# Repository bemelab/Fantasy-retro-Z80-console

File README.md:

# Z80-retro-console

A browser-based Z80 fantasy console with its own programming language (**ZL**), a compiler that produces real Z80 machine code, and emulated display and sound chips. Everything is one self-contained file: `index.html`.

## Run it

Open `index.html` in any modern browser, or turn on GitHub Pages (Settings > Pages > Deploy from a branch > `main` / root) and open the page it gives you.

Press **Run** once so the browser allows sound.

## What is inside

- **CPU:** a full Z80 clocked at 4 MHz: every documented and undocumented instruction, all flags, interrupts (IM 0/1/2, NMI) and exact T-states, with 64 KB of memory. It passes the zexdoc and zexall instruction exercisers.
- **ZL language:** variables, `if`/`else`, `while`, `for`, arrays (1D and 2D), `gosub`/`goto`, `data` tables, sprites, text, and chip commands. It compiles to Z80 machine code.
- **Assembly listing:** every ZL line is shown with the Z80 instructions it produced, with comments.
- **Displays** (choose in the dropdown):
  - Virtual 64x64, 16 colors
  - SSD1306 OLED 128x64 (mono)
  - ST7735 TFT 128x160
  - Nokia 5110 PCD8544 84x48 (mono)
  - MC6845 CRTC text 80x25 and graphics
  - TMS9918A VDP 256x192: Graphics I and II, Text, Multicolor, 32 sprites, status flags
  - MC6847 VDG: text, semigraphics and 8 graphics modes
- **Sound:** AY-3-8910 or AY-3-8912 (pick one in the list) with 3 tone channels, noise, mixer, envelope (16 shapes), I/O port A, and port B on the AY-3-8910. There is also a simple `beep`.

## Examples

Pick one from the example list: alien attack game, Neon Rain (AY music), chip showcase (TMS9918A + AY), bouncing balls with 2D arrays, Game of Life, CRTC text scrolling, and more.

## ZL at a glance

```
x = 5                    ; variables are 8-bit
dim a 4                  ; arrays
data a 10 20 30 40       ; fill an array
for i = 0 to 4
  plot i i 11            ; x y color
end
label main
  key k                  ; arrows and fire as bits
  beep 40
  wait 1
  goto main
```

The reference section in the page lists every command.

## Notes

- Values are 8-bit (0 to 255).
- The TMS9918A and MC6847 keep pixels in their own memory layouts. `plot` works through helper ports, and the TMS9918A keeps its two-colors-per-8-pixels limit.
- Built with the help of Claude.

## Example programs

The example programs are stored as plain text in the `examples/` folder (`.zl` files). Paste one into the editor of the console to run it.

Other files: `cpc464/catch.bas` (a BASIC game for the Amstrad CPC464) and `docs/` (notes on how Snake and Boulder Dash work).

## Real hardware

`docs/hardware.md` is the plan for a real ZL-80 board: Z80, TMS9918A video, AY-3-8910 sound, 512 KB flash and 512 KB RAM, a PS/2 PC keyboard and two joysticks, and SCART output to a TV. Its KiCad schematic is in `hardware/kicad/`.

The board is 138 x 105 mm with 4 layers. It has not been built yet.

| Top | Bottom |
|---|---|
|  |  |

PCB layout: [all copper layers](hardware/images/pcb-layout.svg), [top](hardware/images/pcb-top-copper.svg), [inner signal layer In2](hardware/images/pcb-inner2-copper.svg), [bottom](hardware/images/pcb-bottom-copper.svg).

Schematic pages (click for full size):

| | |
|---|---|
|  Overview |  CPU, memory and decoding |
|  Video: TMS9918A and VRAM |  Sound and joysticks |
|  Keyboard and USB |  Power, reset and TV |

Pick **ZL-80 board (real hardware)** in the display list to run a program on an exact copy of that board: Z80 at 3.58 MHz, paged memory, a kernel ROM, only the real I/O ports, and the frame interrupt. A program that runs there is meant to run on the real board unchanged.

In that display, **ROM .bin** saves a 512 KB flash image for an EEPROM programmer and **HEX** saves the program as Intel HEX. **Send to board** sends the program to a real board over its USB port (Web Serial, Chrome or Edge), and **Send to emulator** sends it the same way to the emulated board. The real-board path has not been tried on hardware yet.

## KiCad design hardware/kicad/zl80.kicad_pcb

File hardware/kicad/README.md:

# ZL-80 board schematic

The KiCad schematic of the board described in [docs/hardware.md](../../docs/hardware.md).

**Not built or tested.** Check every pin against the datasheets before you order a board.

Pictures of every schematic page, the copper layers and the 3D views are in [hardware/images](../images). They are exported with `kicad-cli` (`sch export svg`, `pcb export svg`, `pcb render`); export them again after changing the board.

| File | What it is |
|---|---|
| `zl80.kicad_pro`, `zl80.kicad_sch` | The KiCad project and its root sheet (KiCad 7 format; KiCad 8 and 9 open it). The root sheet has one box per page; double-click a box to open the page. |
| `cpu_memory.kicad_sch` | Page 2: Z80, flash, SRAM, page registers, I/O decoding. |
| `video.kicad_sch` | Page 3: TMS9918A, VRAM (62256 and latches), crystal, video output stage. |
| `sound.kicad_sch` | Page 4: AY-3-8910, its bus control, joystick multiplexers, DB9 ports, audio mix. |
| `keyboard_usb.kicad_sch` | Page 5: 82C55, ATmega328P and the PS/2 header, expansion header, FT245RL USB FIFO and USB-C socket. |
| `power_tv.kicad_sch` | Page 6: 12 V input, 5 V regulator, reset, and the TV header for a SCART cable. |
| `zl80.kicad_sym`, `sym-lib-table` | The board's symbols as a project library, so KiCad finds the `zl80` library. |
| `gen_schematic.py` | Generates the schematic. Change the circuit here, not in KiCad. |
| `sch.py` | The small schematic writer that `gen_schematic.py` uses. |
| `check_schematic.py` | Checks that the file parses and that every pin is either connected or marked as not connected. |
| `zl80-netlist.txt` | Every net with the pins on it, for checking against datasheets. |
| `check_footprints.py` | Checks that every part's footprint exists in KiCad's library and has a pad for each symbol pin. |
| `zl80.kicad_pcb` | The routed 4-layer board, 138 x 105 mm: tracks on F.Cu, In2.Cu and B.Cu, a whole GND plane on In1.Cu, a +5V fill on In2.Cu. |
| `zl80.dsn`, `zl80.ses` | What went to Freerouting and the routes it sent back. `gen_pcb.py import zl80.ses` restores the tracks after `gen_pcb.py` has placed the parts again. |
| `gen_pcb.py` | Builds the board with KiCad's Python: places the parts, draws the outline and planes, writes `zl80.dsn` for Freerouting, and reads the routed `.ses` back. |

To regenerate the schematic and run the check:

```
python gen_schematic.py
python check_schematic.py
```

With KiCad installed, also run its electrical rules check; it should report 0 violations. The netlist KiCad exports has the same 187 nets as `zl80-netlist.txt` (KiCad leaves out the PWR_FLAG markers).

```
kicad-cli sch erc --severity-all zl80.kicad_sch
```

## The PCB

`gen_pcb.py` runs with KiCad's own Python (KiCad's `bin` folder must be on PATH). It reads the parts and nets from `gen_schematic.py`, so the board always matches the schematic.

```
set PATH=D:\Program Files\KiCad\9.0\bin;%PATH%
python gen_pcb.py                      (KiCad's python.exe) places the parts, writes zl80.kicad_pcb and zl80.dsn
freerouting-cli -de zl80.dsn -do zl80.ses -mp 100
python gen_pcb.py import zl80.ses      adds the routed tracks to zl80.kicad_pcb
kicad-cli pcb drc zl80.kicad_pcb
```

Freerouting 2.5.0 routed the board in about 25 minutes (`-mp 200`). Two settings in the DSN that `gen_pcb.py` writes make that work: only the GND net may use In1.Cu, so the GND plane stays whole and GND pads reach it through vias, and the routing boundary sits 0.55 mm inside the board edge. KiCad's DRC with the schematic parity check reports 0 violations, 0 unconnected pads and 0 footprint errors; what is left are silkscreen warnings (labels over pads and over each other), which the board maker clips.

Placement: the 12 V jack, the regulator, the USB-C socket and both joystick ports along the top edge; below them one row of the four DIP-40 sockets (82C55, Z80, TMS9918A, AY-3-8910 from left to right); each group's surface-mount parts are packed beside and below its socket, each chip next to its own 100 nF capacitor. All surface-mount parts are on the top side, so the board needs assembly on one side only. Design rules: 0.15 mm clearance, 0.2 mm tracks, 0.6/0.3 mm vias, all inside JLCPCB's 4-layer limits.

## How the schematic is drawn

- Each chip is a box with a short wire and a net label on every pin. Pins with the same label are connected; there are no long wires.
- A signal that goes to another page has a global label (the label in a frame); KiCad lists the pages it reaches next to it. Signals that stay on one page have plain labels.
- Each chip's 100 nF decoupling capacitor is on the same page; its value says which chip it belongs to, for example `100n (U15)`.
- Active-low signals use KiCad's overbar syntax, for example `~{RD}`.
- The symbols are defined inside the schematic file, so no KiCad library is needed. Footprints are standard KiCad names for through-hole parts. The connectors (SCART, DB9, PS/2) have no footprint yet: pick the ones that match the parts you buy.

## Sources for the pinouts and circuits

- TMS9918A pins, the VRAM circuit (62256 SRAM, three 74HCT574 latches) and the video output stage: TI's TMS9918A data manual and [jblang/TMS9918A](https://github.com/jblang/TMS9918A).
- AY-3-8910 pins and bus control: the General Instrument datasheet and [electrified/rc2014-ym2149](https://github.com/electrified/rc2014-ym2149).
- FT245RL pins and its self-powered circuit: FTDI DS_FT245R (FT_000052) v2.14, the SSOP-28 pin table and figure 6.2.
- SMD packages: Microchip DS20005022F (SST39SF040 PLCC-32), DS40002061B (ATmega328P TQFP-32), Alliance AS6C4008 and AS6C62256, onsemi MMBT4401, GCT USB4105 drawing.
- Other chips: the manufacturers' datasheets (Zilog, Microchip, Alliance, Renesas, TI).

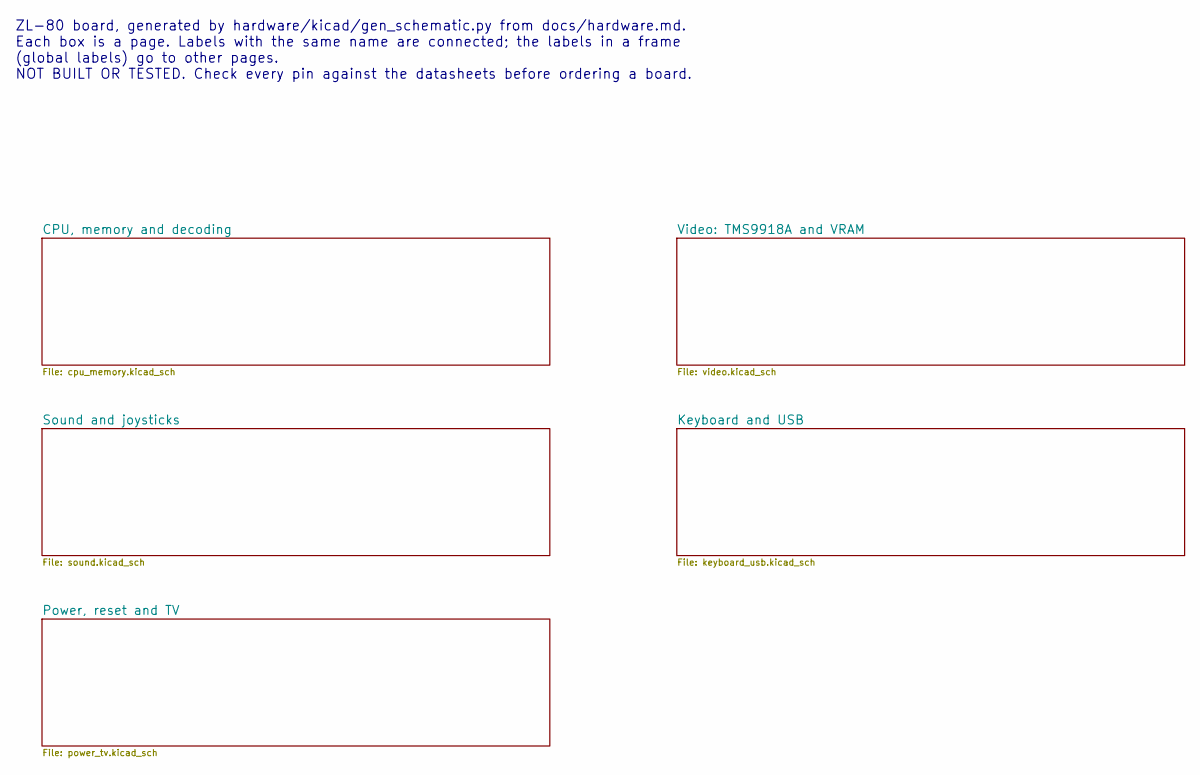
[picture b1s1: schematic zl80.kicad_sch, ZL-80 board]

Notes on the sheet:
ZL-80 board, generated by hardware/kicad/gen_schematic.py from docs/hardware.md. Each box is a page. Labels with the same name are connected; the labels in a frame (global labels) go to other pages. NOT BUILT OR TESTED. Check every pin against the datasheets before ordering a board.

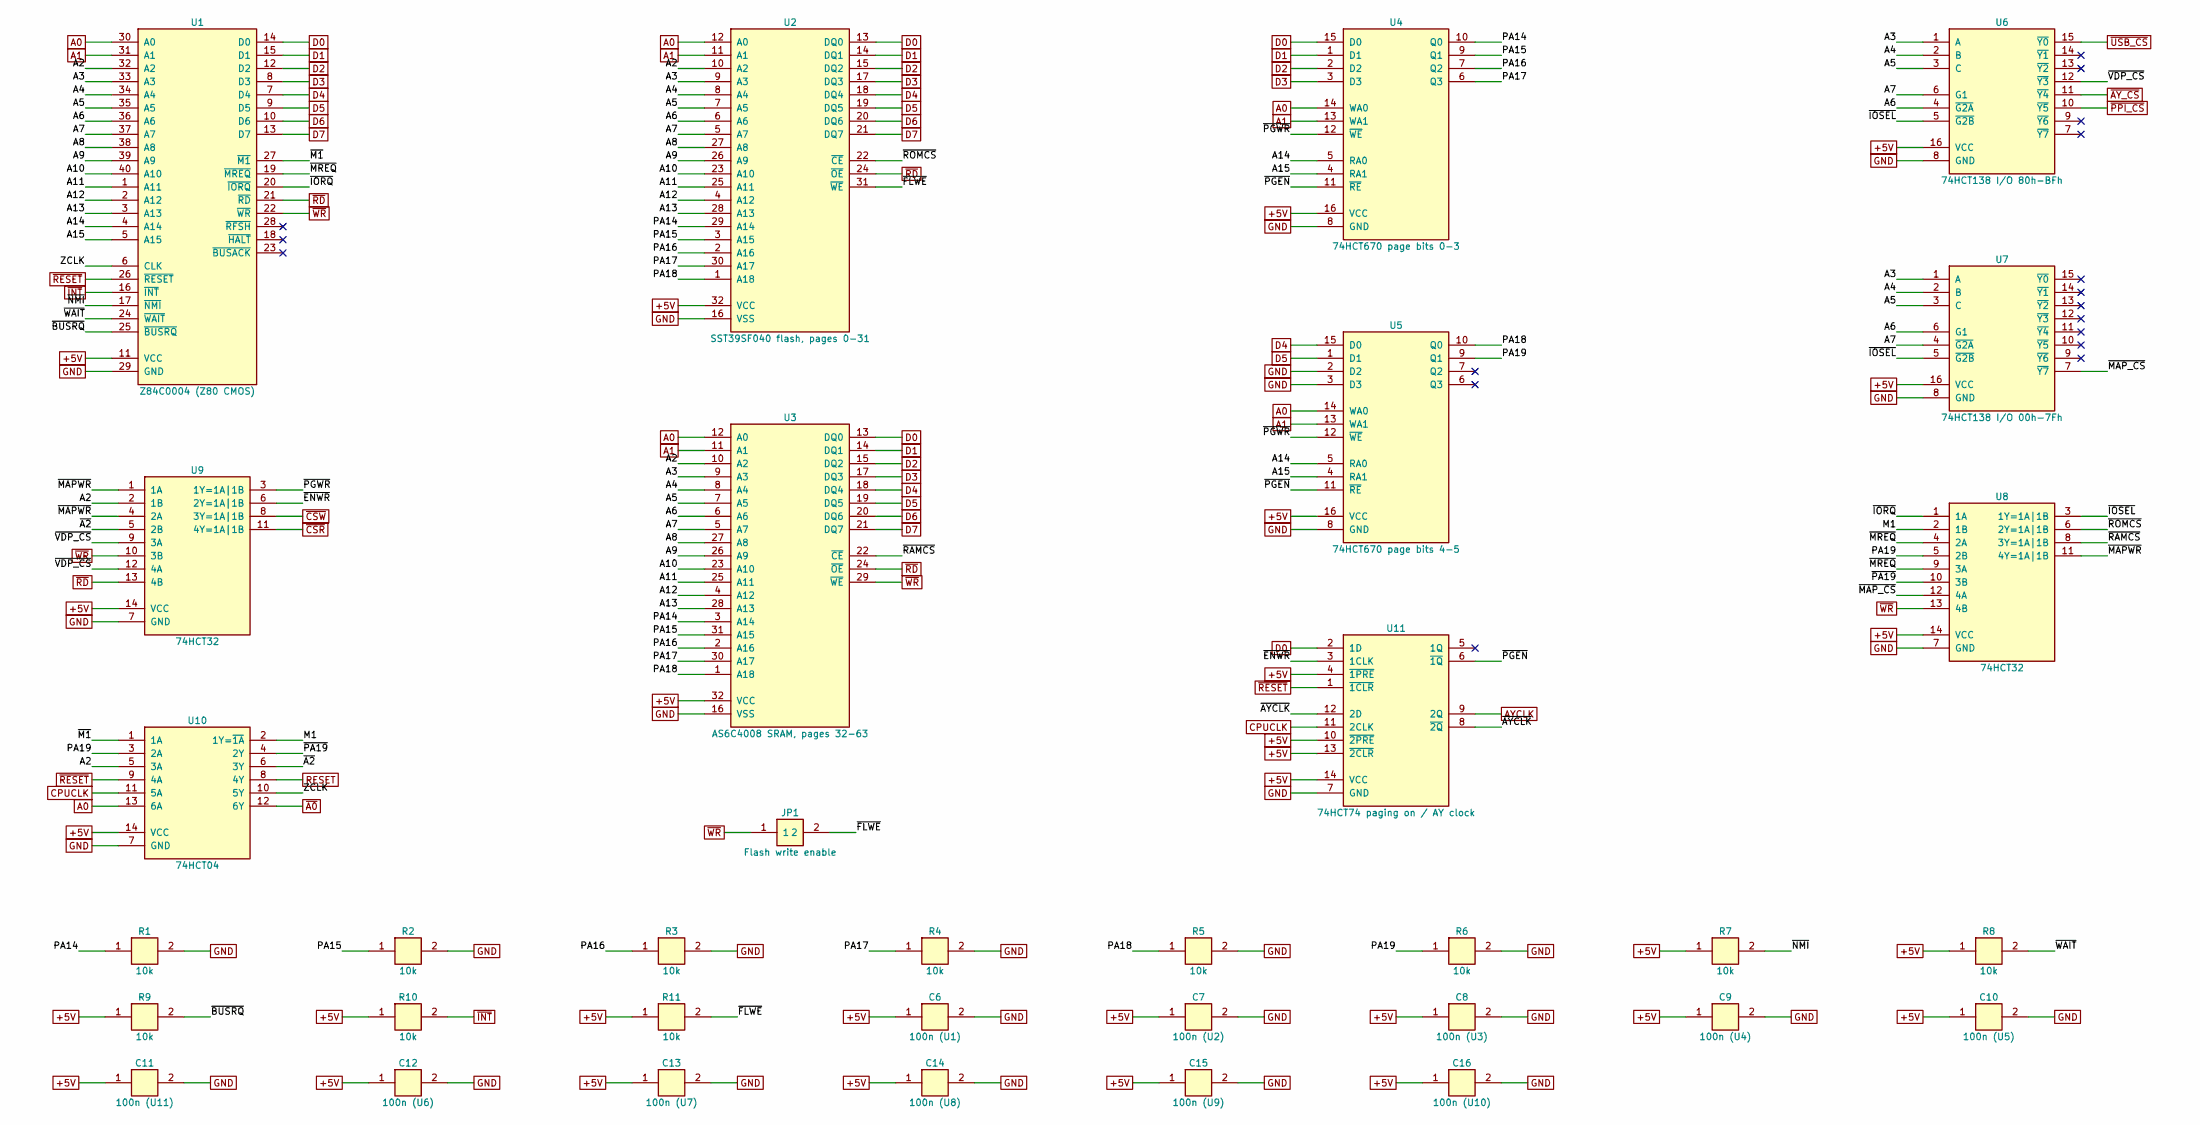
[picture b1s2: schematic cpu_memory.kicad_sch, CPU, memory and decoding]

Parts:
C6: 100n (U1); C_0805_2012Metric
C7: 100n (U2); C_0805_2012Metric
C8: 100n (U3); C_0805_2012Metric
C9: 100n (U4); C_0805_2012Metric
C10: 100n (U5); C_0805_2012Metric
C11: 100n (U11); C_0805_2012Metric
C12: 100n (U6); C_0805_2012Metric
C13: 100n (U7); C_0805_2012Metric
C14: 100n (U8); C_0805_2012Metric
C15: 100n (U9); C_0805_2012Metric
C16: 100n (U10); C_0805_2012Metric
JP1: Flash write enable; SolderJumper-2_P1.3mm_Open_TrianglePad1.0x1.5mm
R1, R2, R3, R4, R5, R6, R7, R8, R9, R10, R11: 10k; R_0805_2012Metric
U1: Z84C0004 (Z80 CMOS); DIP-40_W15.24mm_Socket
U2: SST39SF040 flash, pages 0-31; DIP-32_W15.24mm_Socket
U3: AS6C4008 SRAM, pages 32-63; SOP-32_11.305x20.495mm_P1.27mm
U4: 74HCT670 page bits 0-3; SOIC-16_3.9x9.9mm_P1.27mm
U5: 74HCT670 page bits 4-5; SOIC-16_3.9x9.9mm_P1.27mm
U6: 74HCT138 I/O 80h-BFh; SOIC-16_3.9x9.9mm_P1.27mm
U7: 74HCT138 I/O 00h-7Fh; SOIC-16_3.9x9.9mm_P1.27mm
U8, U9: 74HCT32; SOIC-14_3.9x8.7mm_P1.27mm
U10: 74HCT04; SOIC-14_3.9x8.7mm_P1.27mm
U11: 74HCT74 paging on / AY clock; SOIC-14_3.9x8.7mm_P1.27mm

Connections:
+5V: C6.1, C7.1, C8.1, C9.1, C10.1, C11.1, C12.1, C13.1, C14.1, C15.1, C16.1, R7.1, R8.1, R9.1, R10.1, R11.1, U1.11 (VCC), U2.32 (VCC), U3.32 (VCC), U4.16 (VCC), U5.16 (VCC), U6.16 (VCC), U7.16 (VCC), U8.14 (VCC), U9.14 (VCC), U10.14 (VCC), U11.4 (~1PRE), U11.10 (~2PRE), U11.13 (~2CLR), U11.14 (VCC); also elsewhere on the board
A0: U1.30 (A0), U2.12 (A0), U3.12 (A0), U4.14 (WA0), U5.14 (WA0), U10.13 (6A); also elsewhere on the board
A1: U1.31 (A1), U2.11 (A1), U3.11 (A1), U4.13 (WA1), U5.13 (WA1); also elsewhere on the board
A2: U1.32 (A2), U2.10 (A2), U3.10 (A2), U9.2 (1B), U10.5 (3A)
A3: U1.33 (A3), U2.9 (A3), U3.9 (A3), U6.1 (A), U7.1 (A)
A4: U1.34 (A4), U2.8 (A4), U3.8 (A4), U6.2 (B), U7.2 (B)
A5: U1.35 (A5), U2.7 (A5), U3.7 (A5), U6.3 (C), U7.3 (C)
A6: U1.36 (A6), U2.6 (A6), U3.6 (A6), U6.4 (~G2A), U7.6 (G1)
A7: U1.37 (A7), U2.5 (A7), U3.5 (A7), U6.6 (G1), U7.4 (~G2A)
A8: U1.38 (A8), U2.27 (A8), U3.27 (A8)
A9: U1.39 (A9), U2.26 (A9), U3.26 (A9)
A10: U1.40 (A10), U2.23 (A10), U3.23 (A10)
A11: U1.1 (A11), U2.25 (A11), U3.25 (A11)
A12: U1.2 (A12), U2.4 (A12), U3.4 (A12)
A13: U1.3 (A13), U2.28 (A13), U3.28 (A13)
A14: U1.4 (A14), U4.5 (RA0), U5.5 (RA0)
A15: U1.5 (A15), U4.4 (RA1), U5.4 (RA1)
AYCLK: U11.9 (2Q); also elsewhere on the board
CPUCLK: U10.11 (5A), U11.11 (2CLK); also elsewhere on the board
D0: U1.14 (D0), U2.13 (DQ0), U3.13 (DQ0), U4.15 (D0), U11.2 (1D); also elsewhere on the board
D1: U1.15 (D1), U2.14 (DQ1), U3.14 (DQ1), U4.1 (D1); also elsewhere on the board
D2: U1.12 (D2), U2.15 (DQ2), U3.15 (DQ2), U4.2 (D2); also elsewhere on the board
D3: U1.8 (D3), U2.17 (DQ3), U3.17 (DQ3), U4.3 (D3); also elsewhere on the board
D4: U1.7 (D4), U2.18 (DQ4), U3.18 (DQ4), U5.15 (D0); also elsewhere on the board
D5: U1.9 (D5), U2.19 (DQ5), U3.19 (DQ5), U5.1 (D1); also elsewhere on the board
D6: U1.10 (D6), U2.20 (DQ6), U3.20 (DQ6); also elsewhere on the board
D7: U1.13 (D7), U2.21 (DQ7), U3.21 (DQ7); also elsewhere on the board
GND: C6.2, C7.2, C8.2, C9.2, C10.2, C11.2, C12.2, C13.2, C14.2, C15.2, C16.2, R1.2, R2.2, R3.2, R4.2, R5.2, R6.2, U1.29 (GND), U2.16 (VSS), U3.16 (VSS), U4.8 (GND), U5.2 (D2), U5.3 (D3), U5.8 (GND), U6.8 (GND), U7.8 (GND), U8.7 (GND), U9.7 (GND), U10.7 (GND), U11.7 (GND); also elsewhere on the board
M1: U8.2 (1B), U10.2 (1Y=~1A)
PA14: R1.1, U2.29 (A14), U3.3 (A14), U4.10 (Q0)
PA15: R2.1, U2.3 (A15), U3.31 (A15), U4.9 (Q1)
PA16: R3.1, U2.2 (A16), U3.2 (A16), U4.7 (Q2)
PA17: R4.1, U2.30 (A17), U3.30 (A17), U4.6 (Q3)
PA18: R5.1, U2.1 (A18), U3.1 (A18), U5.10 (Q0)
PA19: R6.1, U5.9 (Q1), U8.5 (2B), U10.3 (2A)
RESET: U10.8 (4Y); also elsewhere on the board
ZCLK: U1.6 (CLK), U10.10 (5Y)
~A0: U10.12 (6Y); also elsewhere on the board
~A2: U9.5 (2B), U10.6 (3Y)
~AYCLK: U11.8 (~2Q), U11.12 (2D)
~AY_CS: U6.11 (~Y4); also elsewhere on the board
~BUSRQ: R9.2, U1.25 (~BUSRQ)
~CSR: U9.11 (4Y=1A|1B); also elsewhere on the board
~CSW: U9.8 (3Y=1A|1B); also elsewhere on the board
~ENWR: U9.6 (2Y=1A|1B), U11.3 (1CLK)
~FLWE: JP1.2, R11.2, U2.31 (~WE)
~INT: R10.2, U1.16 (~INT); also elsewhere on the board
~IORQ: U1.20 (~IORQ), U8.1 (1A)
~IOSEL: U6.5 (~G2B), U7.5 (~G2B), U8.3 (1Y=1A|1B)
~M1: U1.27 (~M1), U10.1 (1A)
~MAPWR: U8.11 (4Y=1A|1B), U9.1 (1A), U9.4 (2A)
~MAP_CS: U7.7 (~Y7), U8.12 (4A)
~MREQ: U1.19 (~MREQ), U8.4 (2A), U8.9 (3A)
~NMI: R7.2, U1.17 (~NMI)
~PA19: U8.10 (3B), U10.4 (2Y)
~PGEN: U4.11 (~RE), U5.11 (~RE), U11.6 (~1Q)
~PGWR: U4.12 (~WE), U5.12 (~WE), U9.3 (1Y=1A|1B)
~PPI_CS: U6.10 (~Y5); also elsewhere on the board
~RAMCS: U3.22 (~CE), U8.8 (3Y=1A|1B)
~RD: U1.21 (~RD), U2.24 (~OE), U3.24 (~OE), U9.13 (4B); also elsewhere on the board
~RESET: U1.26 (~RESET), U10.9 (4A), U11.1 (~1CLR); also elsewhere on the board
~ROMCS: U2.22 (~CE), U8.6 (2Y=1A|1B)
~USB_CS: U6.15 (~Y0); also elsewhere on the board
~VDP_CS: U6.12 (~Y3), U9.9 (3A), U9.12 (4A)
~WAIT: R8.2, U1.24 (~WAIT)
~WR: JP1.1, U1.22 (~WR), U3.29 (~WE), U8.13 (4B), U9.10 (3B); also elsewhere on the board

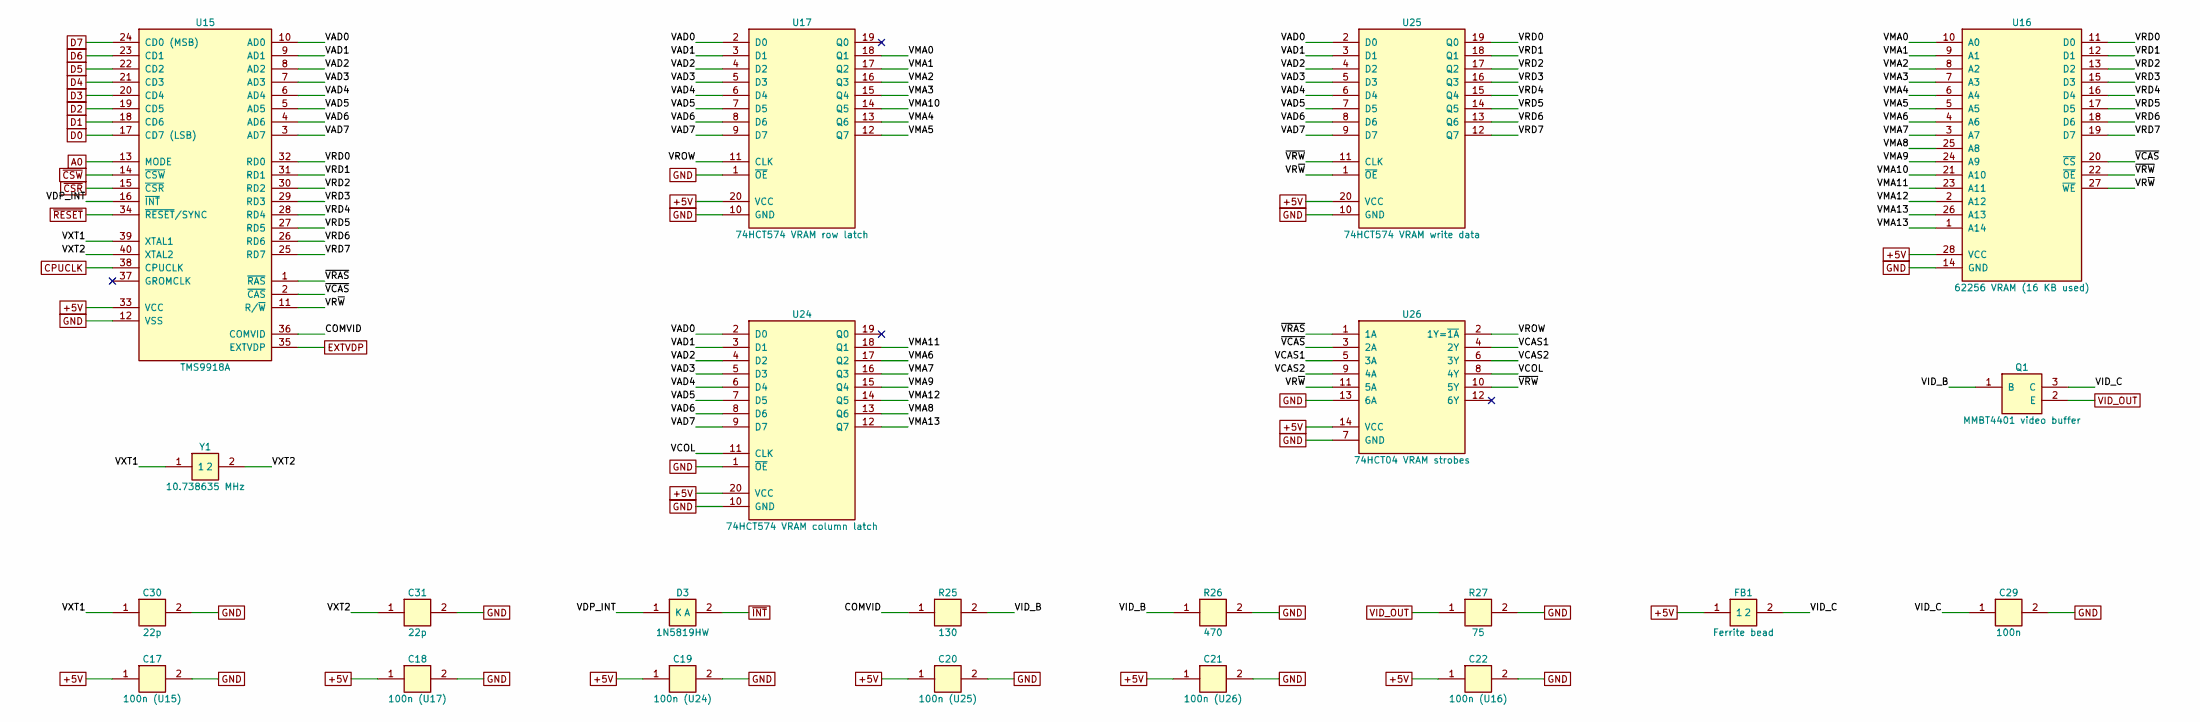
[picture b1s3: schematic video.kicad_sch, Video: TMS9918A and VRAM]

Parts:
C17: 100n (U15); C_0805_2012Metric
C18: 100n (U17); C_0805_2012Metric
C19: 100n (U24); C_0805_2012Metric
C20: 100n (U25); C_0805_2012Metric
C21: 100n (U26); C_0805_2012Metric
C22: 100n (U16); C_0805_2012Metric
C29: 100n; C_0805_2012Metric
C30, C31: 22p; C_0805_2012Metric
D3: 1N5819HW; D_SOD-123
FB1: Ferrite bead; L_0805_2012Metric
Q1: MMBT4401 video buffer; SOT-23-3
R25: 130; R_0805_2012Metric
R26: 470; R_0805_2012Metric
R27: 75; R_0805_2012Metric
U15: TMS9918A; DIP-40_W15.24mm_Socket
U16: 62256 VRAM (16 KB used); SOP-28_8.4x18.16mm_P1.27mm
U17: 74HCT574 VRAM row latch; SOIC-20W_7.5x12.8mm_P1.27mm
U24: 74HCT574 VRAM column latch; SOIC-20W_7.5x12.8mm_P1.27mm
U25: 74HCT574 VRAM write data; SOIC-20W_7.5x12.8mm_P1.27mm
U26: 74HCT04 VRAM strobes; SOIC-14_3.9x8.7mm_P1.27mm
Y1: 10.738635 MHz; Crystal_SMD_HC49-SD

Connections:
+5V: C17.1, C18.1, C19.1, C20.1, C21.1, C22.1, FB1.1, U15.33 (VCC), U16.28 (VCC), U17.20 (VCC), U24.20 (VCC), U25.20 (VCC), U26.14 (VCC); also elsewhere on the board
A0: U15.13 (MODE); also elsewhere on the board
COMVID: R25.1, U15.36 (COMVID)
CPUCLK: U15.38 (CPUCLK); also elsewhere on the board
D0: U15.17 (CD7 (LSB)); also elsewhere on the board
D1: U15.18 (CD6); also elsewhere on the board
D2: U15.19 (CD5); also elsewhere on the board
D3: U15.20 (CD4); also elsewhere on the board
D4: U15.21 (CD3); also elsewhere on the board
D5: U15.22 (CD2); also elsewhere on the board
D6: U15.23 (CD1); also elsewhere on the board
D7: U15.24 (CD0 (MSB)); also elsewhere on the board
EXTVDP: U15.35 (EXTVDP); also elsewhere on the board
GND: C17.2, C18.2, C19.2, C20.2, C21.2, C22.2, C29.2, C30.2, C31.2, R26.2, R27.2, U15.12 (VSS), U16.14 (GND), U17.1 (~OE), U17.10 (GND), U24.1 (~OE), U24.10 (GND), U25.10 (GND), U26.7 (GND), U26.13 (6A); also elsewhere on the board
VAD0: U15.10 (AD0), U17.2 (D0), U24.2 (D0), U25.2 (D0)
VAD1: U15.9 (AD1), U17.3 (D1), U24.3 (D1), U25.3 (D1)
VAD2: U15.8 (AD2), U17.4 (D2), U24.4 (D2), U25.4 (D2)
VAD3: U15.7 (AD3), U17.5 (D3), U24.5 (D3), U25.5 (D3)
VAD4: U15.6 (AD4), U17.6 (D4), U24.6 (D4), U25.6 (D4)
VAD5: U15.5 (AD5), U17.7 (D5), U24.7 (D5), U25.7 (D5)
VAD6: U15.4 (AD6), U17.8 (D6), U24.8 (D6), U25.8 (D6)
VAD7: U15.3 (AD7), U17.9 (D7), U24.9 (D7), U25.9 (D7)
VCAS1: U26.4 (2Y), U26.5 (3A)
VCAS2: U26.6 (3Y), U26.9 (4A)
VCOL: U24.11 (CLK), U26.8 (4Y)
VDP_INT: D3.1 (K), U15.16 (~INT)
VID_B: Q1.1 (B), R25.2, R26.1
VID_C: C29.1, FB1.2, Q1.3 (C)
VID_OUT: Q1.2 (E), R27.1; also elsewhere on the board
VMA0: U16.10 (A0), U17.18 (Q1)
VMA1: U16.9 (A1), U17.17 (Q2)
VMA2: U16.8 (A2), U17.16 (Q3)
VMA3: U16.7 (A3), U17.15 (Q4)
VMA4: U16.6 (A4), U17.13 (Q6)
VMA5: U16.5 (A5), U17.12 (Q7)
VMA6: U16.4 (A6), U24.17 (Q2)
VMA7: U16.3 (A7), U24.16 (Q3)
VMA8: U16.25 (A8), U24.13 (Q6)
VMA9: U16.24 (A9), U24.15 (Q4)
VMA10: U16.21 (A10), U17.14 (Q5)
VMA11: U16.23 (A11), U24.18 (Q1)
VMA12: U16.2 (A12), U24.14 (Q5)
VMA13: U16.1 (A14), U16.26 (A13), U24.12 (Q7)
VRD0: U15.32 (RD0), U16.11 (D0), U25.19 (Q0)
VRD1: U15.31 (RD1), U16.12 (D1), U25.18 (Q1)
VRD2: U15.30 (RD2), U16.13 (D2), U25.17 (Q2)
VRD3: U15.29 (RD3), U16.15 (D3), U25.16 (Q3)
VRD4: U15.28 (RD4), U16.16 (D4), U25.15 (Q4)
VRD5: U15.27 (RD5), U16.17 (D5), U25.14 (Q5)
VRD6: U15.26 (RD6), U16.18 (D6), U25.13 (Q6)
VRD7: U15.25 (RD7), U16.19 (D7), U25.12 (Q7)
VROW: U17.11 (CLK), U26.2 (1Y=~1A)
VR~W: U15.11 (R/~W), U16.27 (~WE), U25.1 (~OE), U26.11 (5A)
VXT1: C30.1, U15.39 (XTAL1), Y1.1
VXT2: C31.1, U15.40 (XTAL2), Y1.2
~CSR: U15.15 (~CSR); also elsewhere on the board
~CSW: U15.14 (~CSW); also elsewhere on the board
~INT: D3.2 (A); also elsewhere on the board
~RESET: U15.34 (~RESET/SYNC); also elsewhere on the board
~VCAS: U15.2 (~CAS), U16.20 (~CS), U26.3 (2A)
~VRAS: U15.1 (~RAS), U26.1 (1A)
~VRW: U16.22 (~OE), U25.11 (CLK), U26.10 (5Y)

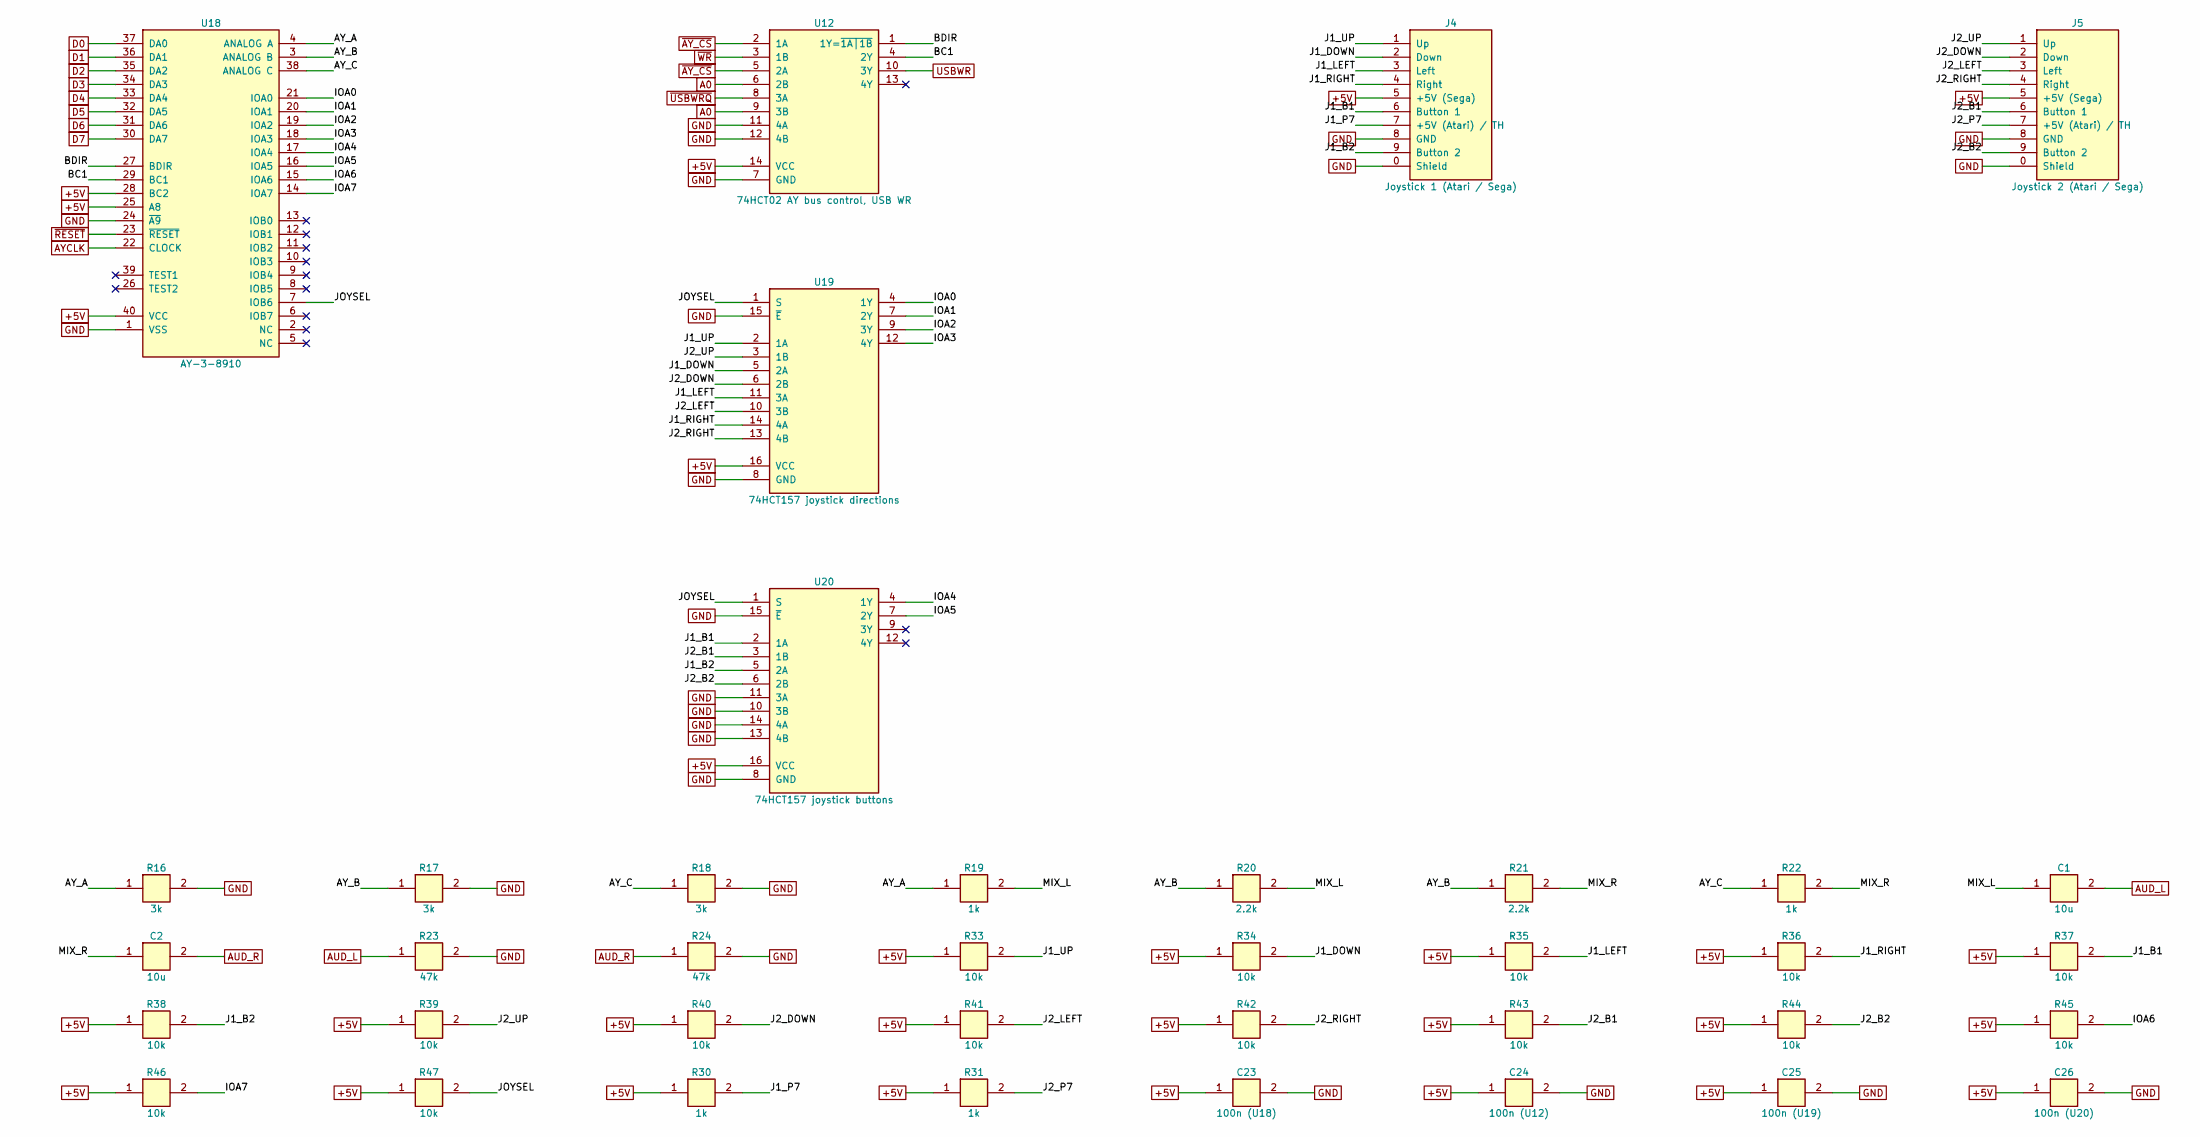
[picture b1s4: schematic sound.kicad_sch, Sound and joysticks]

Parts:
C1, C2: 10u; C_0805_2012Metric
C23: 100n (U18); C_0805_2012Metric
C24: 100n (U12); C_0805_2012Metric
C25: 100n (U19); C_0805_2012Metric
C26: 100n (U20); C_0805_2012Metric
J4: Joystick 1 (Atari / Sega); DSUB-9_Male_Horizontal_P2.77x2.84mm_EdgePinOffset7.70mm_Hou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
J5: Joystick 2 (Atari / Sega); DSUB-9_Male_Horizontal_P2.77x2.84mm_EdgePinOffset7.70mm_Hou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
R16, R17, R18: 3k; R_0805_2012Metric
R19, R22, R30, R31: 1k; R_0805_2012Metric
R20, R21: 2.2k; R_0805_2012Metric
R23, R24: 47k; R_0805_2012Metric
R33, R34, R35, R36, R37, R38, R39, R40, R41, R42, R43, R44, R45, R46, R47: 10k; R_0805_2012Metric
U12: 74HCT02 AY bus control, USB WR; SOIC-14_3.9x8.7mm_P1.27mm
U18: AY-3-8910; DIP-40_W15.24mm_Socket
U19: 74HCT157 joystick directions; SOIC-16_3.9x9.9mm_P1.27mm
U20: 74HCT157 joystick buttons; SOIC-16_3.9x9.9mm_P1.27mm

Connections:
+5V: C23.1, C24.1, C25.1, C26.1, J4.5 (+5V (Sega)), J5.5 (+5V (Sega)), R30.1, R31.1, R33.1, R34.1, R35.1, R36.1, R37.1, R38.1, R39.1, R40.1, R41.1, R42.1, R43.1, R44.1, R45.1, R46.1, R47.1, U12.14 (VCC), U18.25 (A8), U18.28 (BC2), U18.40 (VCC), U19.16 (VCC), U20.16 (VCC); also elsewhere on the board
A0: U12.6 (2B), U12.9 (3B); also elsewhere on the board
AUD_L: C1.2, R23.1; also elsewhere on the board
AUD_R: C2.2, R24.1; also elsewhere on the board
AYCLK: U18.22 (CLOCK); also elsewhere on the board
AY_A: R16.1, R19.1, U18.4 (ANALOG A)
AY_B: R17.1, R20.1, R21.1, U18.3 (ANALOG B)
AY_C: R18.1, R22.1, U18.38 (ANALOG C)
BC1: U12.4 (2Y), U18.29 (BC1)
BDIR: U12.1 (1Y=~1A|1B), U18.27 (BDIR)
D0: U18.37 (DA0); also elsewhere on the board
D1: U18.36 (DA1); also elsewhere on the board
D2: U18.35 (DA2); also elsewhere on the board
D3: U18.34 (DA3); also elsewhere on the board
D4: U18.33 (DA4); also elsewhere on the board
D5: U18.32 (DA5); also elsewhere on the board
D6: U18.31 (DA6); also elsewhere on the board
D7: U18.30 (DA7); also elsewhere on the board
GND: C23.2, C24.2, C25.2, C26.2, J4.0 (Shield), J4.8 (GND), J5.0 (Shield), J5.8 (GND), R16.2, R17.2, R18.2, R23.2, R24.2, U12.7 (GND), U12.11 (4A), U12.12 (4B), U18.1 (VSS), U18.24 (~A9), U19.8 (GND), U19.15 (~E), U20.8 (GND), U20.10 (3B), U20.11 (3A), U20.13 (4B), U20.14 (4A), U20.15 (~E); also elsewhere on the board
IOA0: U18.21 (IOA0), U19.4 (1Y)
IOA1: U18.20 (IOA1), U19.7 (2Y)
IOA2: U18.19 (IOA2), U19.9 (3Y)
IOA3: U18.18 (IOA3), U19.12 (4Y)
IOA4: U18.17 (IOA4), U20.4 (1Y)
IOA5: U18.16 (IOA5), U20.7 (2Y)
IOA6: R45.2, U18.15 (IOA6)
IOA7: R46.2, U18.14 (IOA7)
J1_B1: J4.6 (Button 1), R37.2, U20.2 (1A)
J1_B2: J4.9 (Button 2), R38.2, U20.5 (2A)
J1_DOWN: J4.2 (Down), R34.2, U19.5 (2A)
J1_LEFT: J4.3 (Left), R35.2, U19.11 (3A)
J1_P7: J4.7 (+5V (Atari) / TH), R30.2
J1_RIGHT: J4.4 (Right), R36.2, U19.14 (4A)
J1_UP: J4.1 (Up), R33.2, U19.2 (1A)
J2_B1: J5.6 (Button 1), R43.2, U20.3 (1B)
J2_B2: J5.9 (Button 2), R44.2, U20.6 (2B)
J2_DOWN: J5.2 (Down), R40.2, U19.6 (2B)
J2_LEFT: J5.3 (Left), R41.2, U19.10 (3B)
J2_P7: J5.7 (+5V (Atari) / TH), R31.2
J2_RIGHT: J5.4 (Right), R42.2, U19.13 (4B)
J2_UP: J5.1 (Up), R39.2, U19.3 (1B)
JOYSEL: R47.2, U18.7 (IOB6), U19.1 (S), U20.1 (S)
MIX_L: C1.1, R19.2, R20.2
MIX_R: C2.1, R21.2, R22.2
USBWR: U12.10 (3Y); also elsewhere on the board
~AY_CS: U12.2 (1A), U12.5 (2A); also elsewhere on the board
~RESET: U18.23 (~RESET); also elsewhere on the board
~USBWRQ: U12.8 (3A); also elsewhere on the board
~WR: U12.3 (1B); also elsewhere on the board

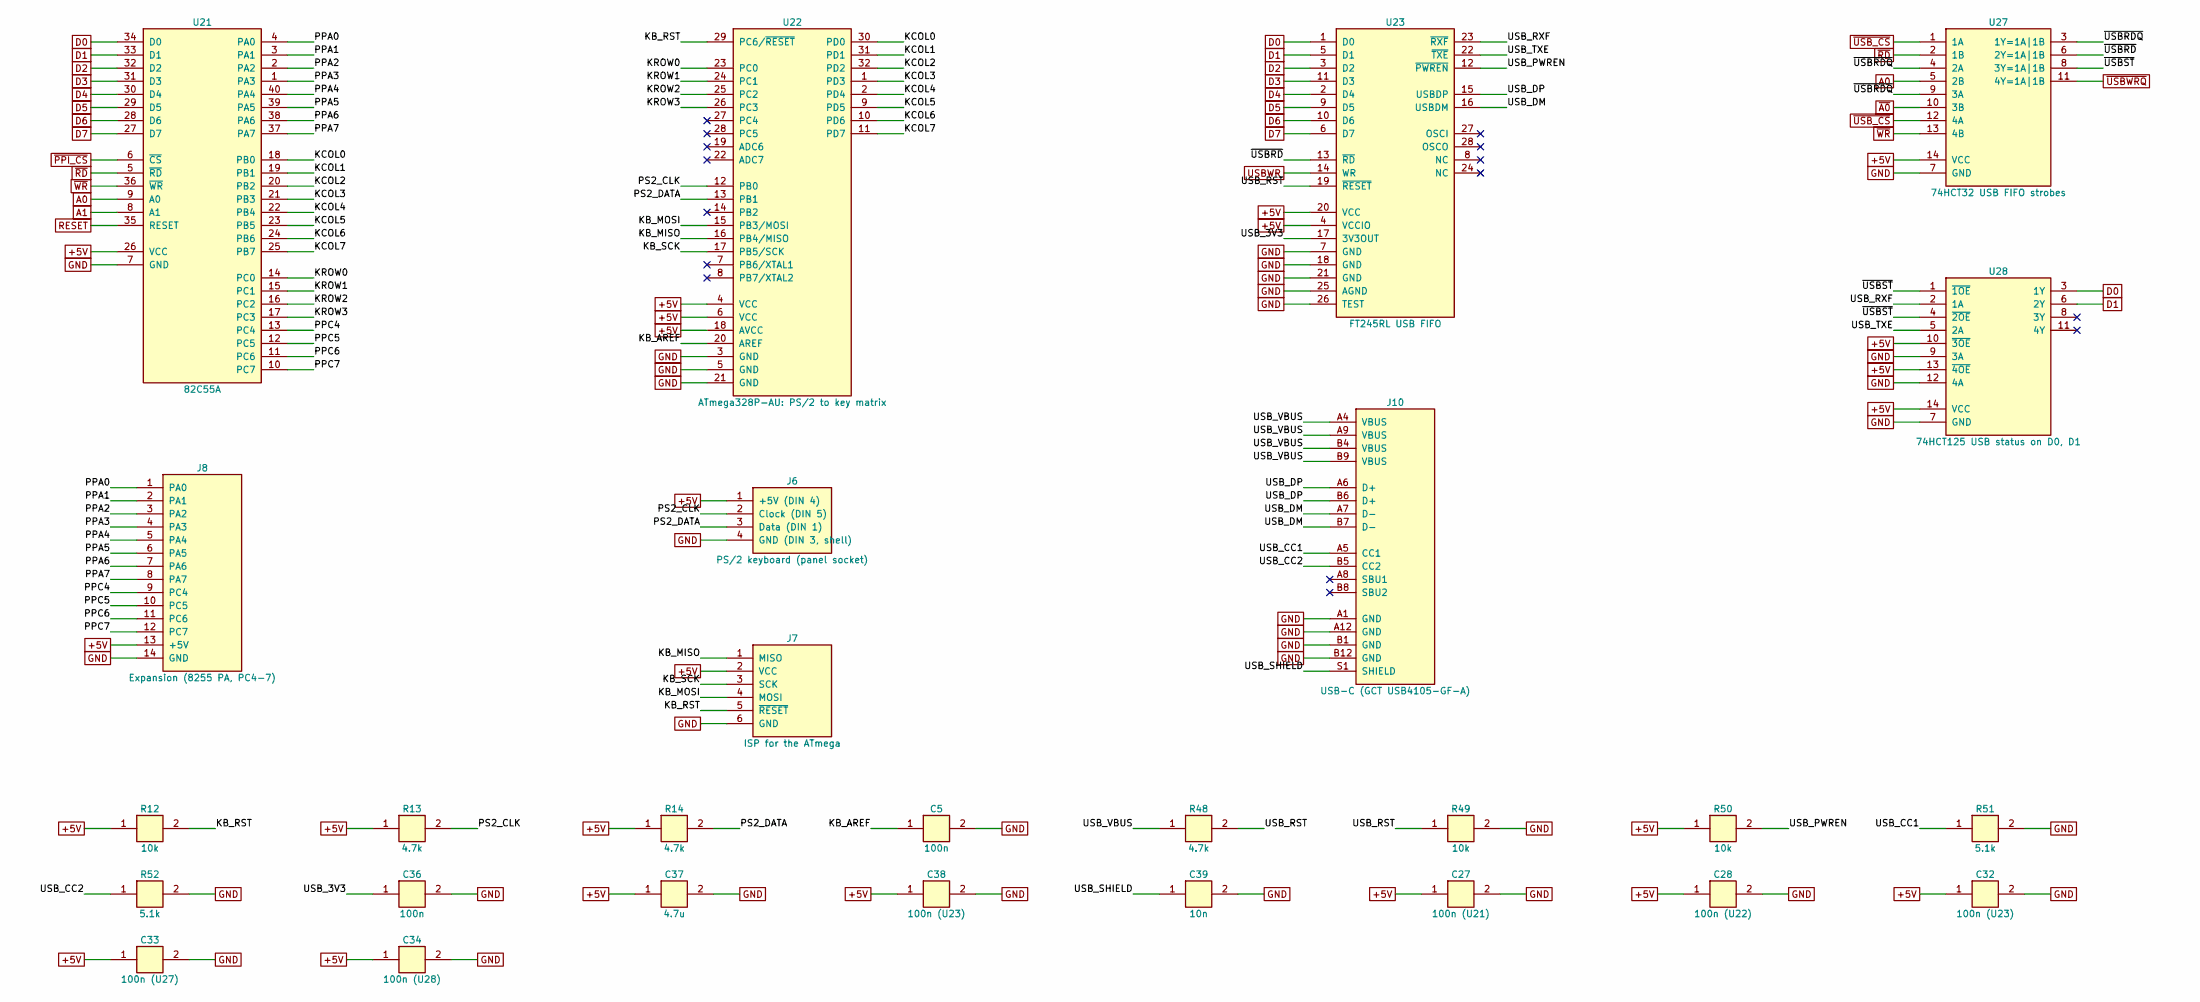
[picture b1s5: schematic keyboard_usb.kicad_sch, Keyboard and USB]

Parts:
C5, C36: 100n; C_0805_2012Metric
C27: 100n (U21); C_0805_2012Metric
C28: 100n (U22); C_0805_2012Metric
C32, C38: 100n (U23); C_0805_2012Metric
C33: 100n (U27); C_0805_2012Metric
C34: 100n (U28); C_0805_2012Metric
C37: 4.7u; C_0805_2012Metric
C39: 10n; C_0805_2012Metric
J6: PS/2 keyboard (panel socket); PinHeader_1x04_P2.54mm_Vertical
J7: ISP for the ATmega; PinHeader_2x03_P2.54mm_Vertical
J8: Expansion (8255 PA, PC4-7); PinHeader_2x07_P2.54mm_Vertical
J10: USB-C (GCT USB4105-GF-A); USB_C_Receptacle_GCT_USB4105-xx-A_16P_TopMnt_Horizontal
R12, R49, R50: 10k; R_0805_2012Metric
R13, R14, R48: 4.7k; R_0805_2012Metric
R51, R52: 5.1k; R_0805_2012Metric
U21: 82C55A; DIP-40_W15.24mm_Socket
U22: ATmega328P-AU: PS/2 to key matrix; TQFP-32_7x7mm_P0.8mm
U23: FT245RL USB FIFO; SSOP-28_5.3x10.2mm_P0.65mm
U27: 74HCT32 USB FIFO strobes; SOIC-14_3.9x8.7mm_P1.27mm
U28: 74HCT125 USB status on D0, D1; SOIC-14_3.9x8.7mm_P1.27mm

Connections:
+5V: C27.1, C28.1, C32.1, C33.1, C34.1, C37.1, C38.1, J6.1 (+5V (DIN 4)), J7.2 (VCC), J8.13 (+5V), R12.1, R13.1, R14.1, R50.1, U21.26 (VCC), U22.4 (VCC), U22.6 (VCC), U22.18 (AVCC), U23.4 (VCCIO), U23.20 (VCC), U27.14 (VCC), U28.10 (~3OE), U28.13 (~4OE), U28.14 (VCC); also elsewhere on the board
A0: U21.9 (A0), U27.5 (2B); also elsewhere on the board
A1: U21.8 (A1); also elsewhere on the board
D0: U21.34 (D0), U23.1 (D0), U28.3 (1Y); also elsewhere on the board
D1: U21.33 (D1), U23.5 (D1), U28.6 (2Y); also elsewhere on the board
D2: U21.32 (D2), U23.3 (D2); also elsewhere on the board
D3: U21.31 (D3), U23.11 (D3); also elsewhere on the board
D4: U21.30 (D4), U23.2 (D4); also elsewhere on the board
D5: U21.29 (D5), U23.9 (D5); also elsewhere on the board
D6: U21.28 (D6), U23.10 (D6); also elsewhere on the board
D7: U21.27 (D7), U23.6 (D7); also elsewhere on the board
GND: C5.2, C27.2, C28.2, C32.2, C33.2, C34.2, C36.2, C37.2, C38.2, C39.2, J6.4 (GND (DIN 3, shell)), J7.6 (GND), J8.14 (GND), J10.A1 (GND), J10.A12 (GND), J10.B1 (GND), J10.B12 (GND), R49.2, R51.2, R52.2, U21.7 (GND), U22.3 (GND), U22.5 (GND), U22.21 (GND), U23.7 (GND), U23.18 (GND), U23.21 (GND), U23.25 (AGND), U23.26 (TEST), U27.7 (GND), U28.7 (GND), U28.9 (3A), U28.12 (4A); also elsewhere on the board
KB_AREF: C5.1, U22.20 (AREF)
KB_MISO: J7.1 (MISO), U22.16 (PB4/MISO)
KB_MOSI: J7.4 (MOSI), U22.15 (PB3/MOSI)
KB_RST: J7.5 (~RESET), R12.2, U22.29 (PC6/~RESET)
KB_SCK: J7.3 (SCK), U22.17 (PB5/SCK)
KCOL0: U21.18 (PB0), U22.30 (PD0)
KCOL1: U21.19 (PB1), U22.31 (PD1)
KCOL2: U21.20 (PB2), U22.32 (PD2)
KCOL3: U21.21 (PB3), U22.1 (PD3)
KCOL4: U21.22 (PB4), U22.2 (PD4)
KCOL5: U21.23 (PB5), U22.9 (PD5)
KCOL6: U21.24 (PB6), U22.10 (PD6)
KCOL7: U21.25 (PB7), U22.11 (PD7)
KROW0: U21.14 (PC0), U22.23 (PC0)
KROW1: U21.15 (PC1), U22.24 (PC1)
KROW2: U21.16 (PC2), U22.25 (PC2)
KROW3: U21.17 (PC3), U22.26 (PC3)
PPA0: J8.1 (PA0), U21.4 (PA0)
PPA1: J8.2 (PA1), U21.3 (PA1)
PPA2: J8.3 (PA2), U21.2 (PA2)
PPA3: J8.4 (PA3), U21.1 (PA3)
PPA4: J8.5 (PA4), U21.40 (PA4)
PPA5: J8.6 (PA5), U21.39 (PA5)
PPA6: J8.7 (PA6), U21.38 (PA6)
PPA7: J8.8 (PA7), U21.37 (PA7)
PPC4: J8.9 (PC4), U21.13 (PC4)
PPC5: J8.10 (PC5), U21.12 (PC5)
PPC6: J8.11 (PC6), U21.11 (PC6)
PPC7: J8.12 (PC7), U21.10 (PC7)
PS2_CLK: J6.2 (Clock (DIN 5)), R13.2, U22.12 (PB0)
PS2_DATA: J6.3 (Data (DIN 1)), R14.2, U22.13 (PB1)
RESET: U21.35 (RESET); also elsewhere on the board
USBWR: U23.14 (WR); also elsewhere on the board
USB_3V3: C36.1, U23.17 (3V3OUT)
USB_CC1: J10.A5 (CC1), R51.1
USB_CC2: J10.B5 (CC2), R52.1
USB_DM: J10.A7 (D-), J10.B7 (D-), U23.16 (USBDM)
USB_DP: J10.A6 (D+), J10.B6 (D+), U23.15 (USBDP)
USB_PWREN: R50.2, U23.12 (~PWREN)
USB_RST: R48.2, R49.1, U23.19 (~RESET)
USB_RXF: U23.23 (~RXF), U28.2 (1A)
USB_SHIELD: C39.1, J10.S1 (SHIELD)
USB_TXE: U23.22 (~TXE), U28.5 (2A)
USB_VBUS: J10.A4 (VBUS), J10.A9 (VBUS), J10.B4 (VBUS), J10.B9 (VBUS), R48.1
~A0: U27.10 (3B); also elsewhere on the board
~PPI_CS: U21.6 (~CS); also elsewhere on the board
~RD: U21.5 (~RD), U27.2 (1B); also elsewhere on the board
~USBRDQ: U27.3 (1Y=1A|1B), U27.4 (2A), U27.9 (3A)
~USBRD: U23.13 (~RD), U27.6 (2Y=1A|1B)
~USBST: U27.8 (3Y=1A|1B), U28.1 (~1OE), U28.4 (~2OE)
~USBWRQ: U27.11 (4Y=1A|1B); also elsewhere on the board
~USB_CS: U27.1 (1A), U27.12 (4A); also elsewhere on the board
~WR: U21.36 (~WR), U27.13 (4B); also elsewhere on the board
